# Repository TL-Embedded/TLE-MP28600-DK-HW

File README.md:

# TLE-MP28600-DK-HW

This is simply a development kit for the MPM MP28600 boost IC.

It promises 600nA IQ, and high efficiency, which should let me run 3V3 systems from a 1S lithium configuration. Considering the datasheet is extremely minimal - I shall have to test for a few things:

 * Output ripple. Ideally this would be low enough that it doesnt mess with my ADC reference.
 * The IQ is consistent across the 2.5 - 4.2V VIN range of 1S.
 * What is the efficiency when in "down mode". Does this just behave as an LDO?

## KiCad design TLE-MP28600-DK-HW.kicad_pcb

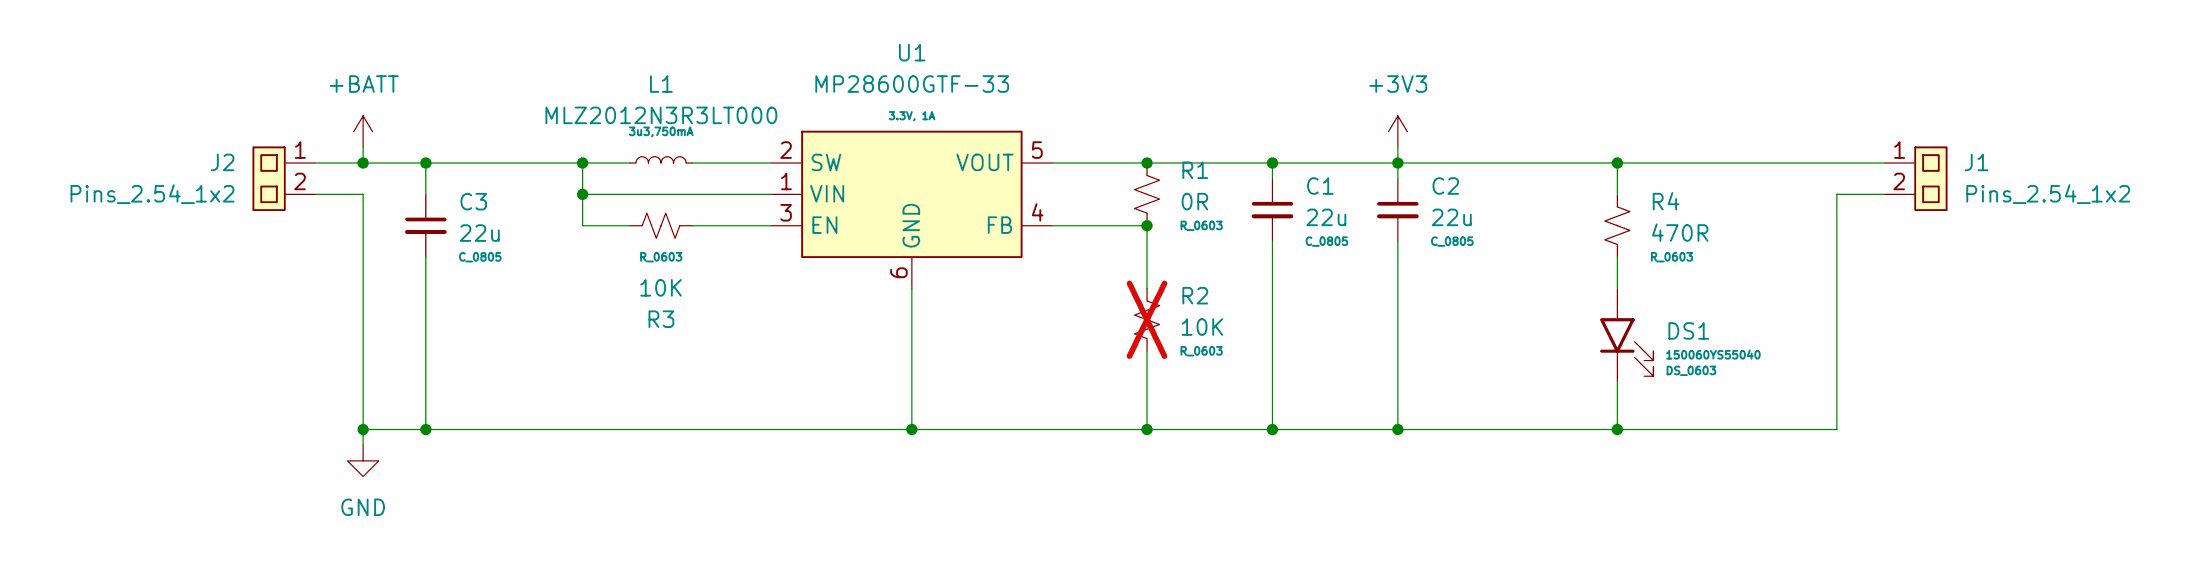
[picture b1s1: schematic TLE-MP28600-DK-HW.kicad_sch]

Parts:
C1, C2, C3: 22u; C_0805
DS1: 150060YS55040; DS_0603
J1, J2: Pins_2.54_1x2; Pins-2.54-1x2
L1: MLZ2012N3R3LT000; FB_0805
R1: 0R; R_0603
R2: 10K; R_0603; not fitted
R3: 10K; R_0603
R4: 470R; R_0603
U1: MP28600GTF-33; SOT563

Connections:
+3V3: C1.1, C2.1, J1.1, R1.1, R4.1, U1.5 (VOUT)
+BATT: C3.1, J2.1, L1.1, R3.1, U1.1 (VIN)
GND: C1.2, C2.2, C3.2, DS1.1 (K), J1.2, J2.2, R2.2, U1.6 (GND)
unnamed: DS1.2 (A), R4.2
unnamed: R3.2, U1.3 (EN)
unnamed: R1.2, R2.1, U1.4 (FB)
unnamed: L1.2, U1.2 (SW)

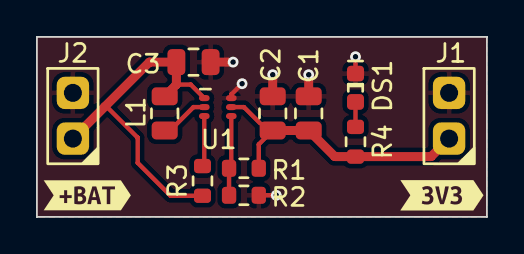
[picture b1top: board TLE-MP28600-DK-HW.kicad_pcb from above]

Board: 2 copper layers, 25.0 x 10.0 mm, 14 parts (0 on the bottom side), 7 nets.

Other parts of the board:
kibuzzard-669A4029: G***; kibuzzard-669A4029
kibuzzard-669A4030: G***; kibuzzard-669A4030

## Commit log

2024-07-19 First version
